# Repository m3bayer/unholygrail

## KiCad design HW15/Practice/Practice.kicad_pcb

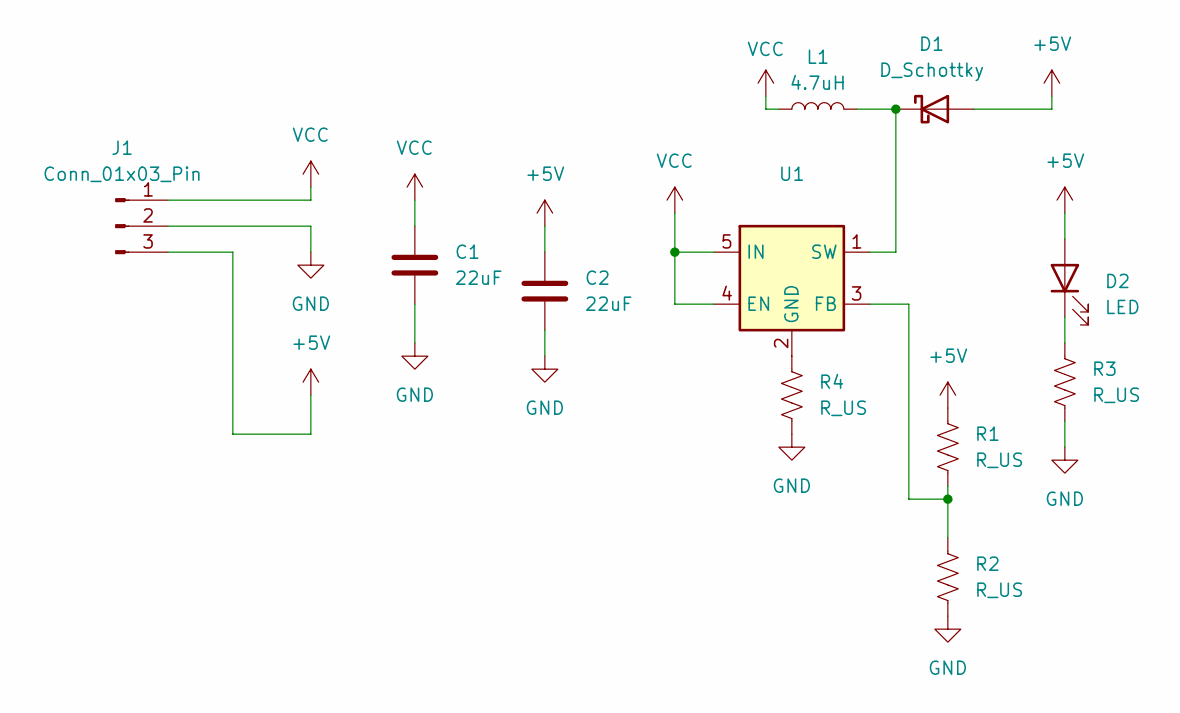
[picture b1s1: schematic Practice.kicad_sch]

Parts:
C1, C2: 22uF; C_0805_2012Metric
D1: D_Schottky; D_SOD-123
D2: LED; LED_D3.0mm
J1: Conn_01x03_Pin; PinSocket_1x03_P2.54mm_Vertical
L1: 4.7uH; L_0402_1005Metric
R1, R2, R3, R4: R_US; R_0805_2012Metric_Pad1.20x1.40mm_HandSolder
U1: MT3608; SOT-23-6

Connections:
+5V: C2.1, D1.2 (A), D2.2 (A), J1.3, R1.1
GND: C1.2, C2.2, J1.2, R2.2, R3.2, R4.2
unnamed: D1.1 (K), L1.2, U1.1 (SW)
unnamed: D2.1 (K), R3.1
unnamed: R1.2, R2.1, U1.3 (FB)
unnamed: R4.1, U1.2 (GND)
VCC: C1.1, J1.1, L1.1, U1.4 (EN), U1.5 (IN)

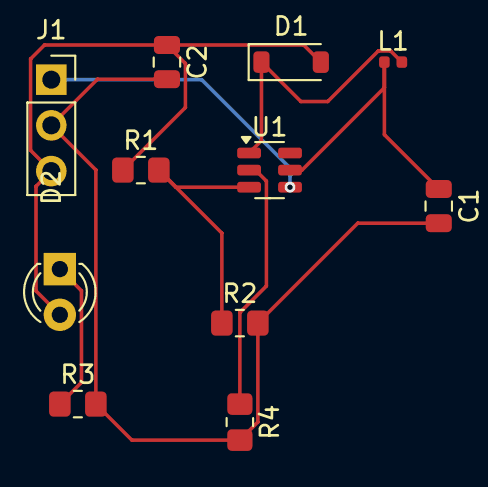
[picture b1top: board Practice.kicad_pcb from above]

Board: 2 copper layers, 11 parts (0 on the bottom side), 7 nets.

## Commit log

2025-04-09 HW2
    HW2
2025-04-09 hw2 update/ hw3
2025-04-09 HW3 Complete
2025-05-12 HW4
    Yay
2025-05-23 Float Math Screenshot
2025-05-25 update for hw7
2025-06-02 HW10
2025-06-02 HW11
2025-06-03 HW12 Update
2025-06-03 HW13
2025-06-03 HW14
2025-06-03 HW15
2025-06-03 HW16++
2025-06-04 HW12 Done
